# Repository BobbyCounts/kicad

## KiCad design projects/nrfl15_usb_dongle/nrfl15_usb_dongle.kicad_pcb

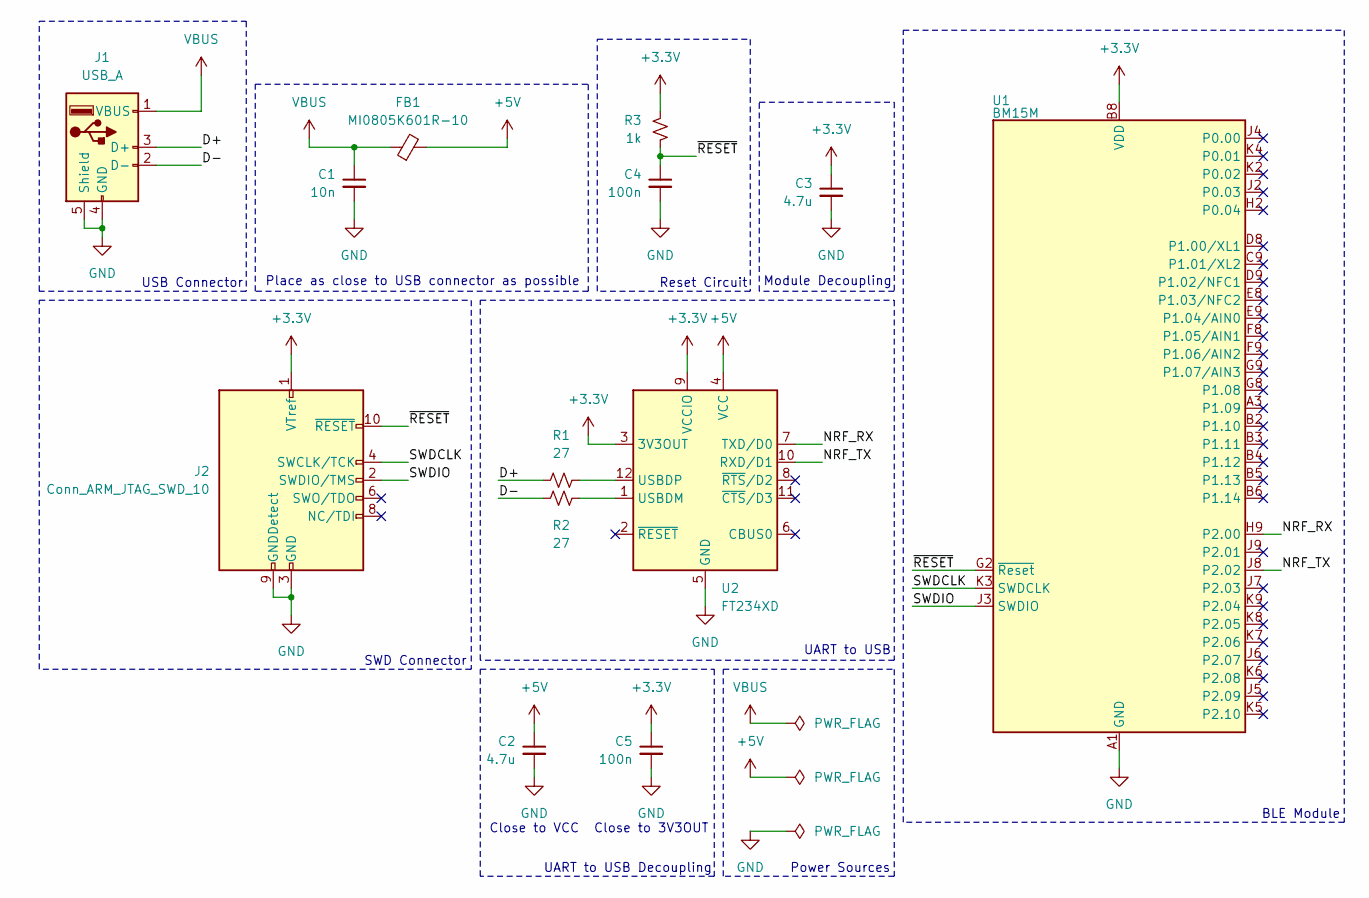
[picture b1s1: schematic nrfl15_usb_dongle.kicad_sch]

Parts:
C1: 10n; C_0402_1005Metric
C2, C3: 4.7u; C_0603_1608Metric
C4, C5: 100n; C_0402_1005Metric
FB1: MI0805K601R-10; L_0805_2012Metric
J1: USB_A; USB_A_Molex_48037-2200_Horizontal
J2: Conn_ARM_JTAG_SWD_10; PinHeader_2x05_P1.27mm_Vertical_SMD
R1, R2: 27; R_0402_1005Metric
R3: 1k; R_0402_1005Metric
U1: BM15M
U2: FT234XD; WDFN-12-1EP_3x3mm_P0.45mm_EP1.7x2.5mm

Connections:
+3.3V: C3.1, C5.1, J2.1 (VTref), R3.1, U1.B8 (VDD), U1.C8 (VDD), U2.3 (3V3OUT), U2.9 (VCCIO)
+5V: C2.1, FB1.2, U2.4 (VCC)
/D+: J1.3 (D+), R1.1
/D-: J1.2 (D-), R2.2
/NRF_RX: U1.H9 (P2.00), U2.7 (TXD/D0)
/NRF_TX: U1.J8 (P2.02), U2.10 (RXD/D1)
/SWDCLK: J2.4 (SWCLK/TCK), U1.K3 (SWDCLK)
/SWDIO: J2.2 (SWDIO/TMS), U1.J3 (SWDIO)
/~RESET: C4.1, J2.10 (~RESET), R3.2, U1.G2 (~Reset)
GND: C1.2, C2.2, C3.2, C4.2, C5.2, J1.4 (GND), J1.5 (Shield), J2.3 (GND), J2.5 (GND), J2.9 (GNDDetect), U1.A1 (GND), U1.A9 (GND), U1.B1 (GND), U1.B7 (GND), U1.B9 (GND), U1.D1 (GND), U1.E1 (GND), U1.F1 (GND), U1.H8 (GND), U2.5 (GND), U2.13 (GND)
unnamed: R2.1, U2.1 (USBDM)
unnamed: R1.2, U2.12 (USBDP)
VBUS: C1.1, FB1.1, J1.1 (VBUS)

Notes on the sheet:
SWD Connector
Module Decoupling
Close to 3V3OUT
Reset Circuit
UART to USB Decoupling
USB Connector
Place as close to USB connector as possible
Power Sources
UART to USB
Close to VCC
BLE Module

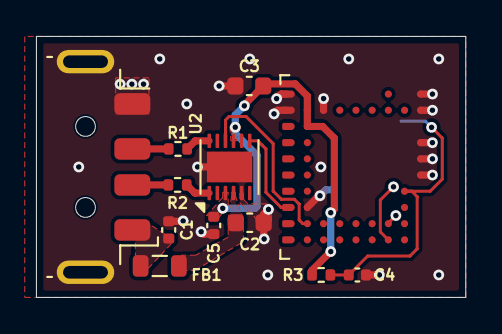
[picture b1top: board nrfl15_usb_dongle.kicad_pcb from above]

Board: 2 copper layers, 23.8 x 14.5 mm, 13 parts (1 on the bottom side), 13 nets.

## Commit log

2025-06-25 Initial
2025-06-25 Add BM15M
2025-06-26 Fix typo in BM15M symbol
2025-06-26 Fix pin position
2025-06-26 Ignore project level backups
2025-06-26 Add nrfl15 usb dongle project
2025-06-26 Hide connector silk
